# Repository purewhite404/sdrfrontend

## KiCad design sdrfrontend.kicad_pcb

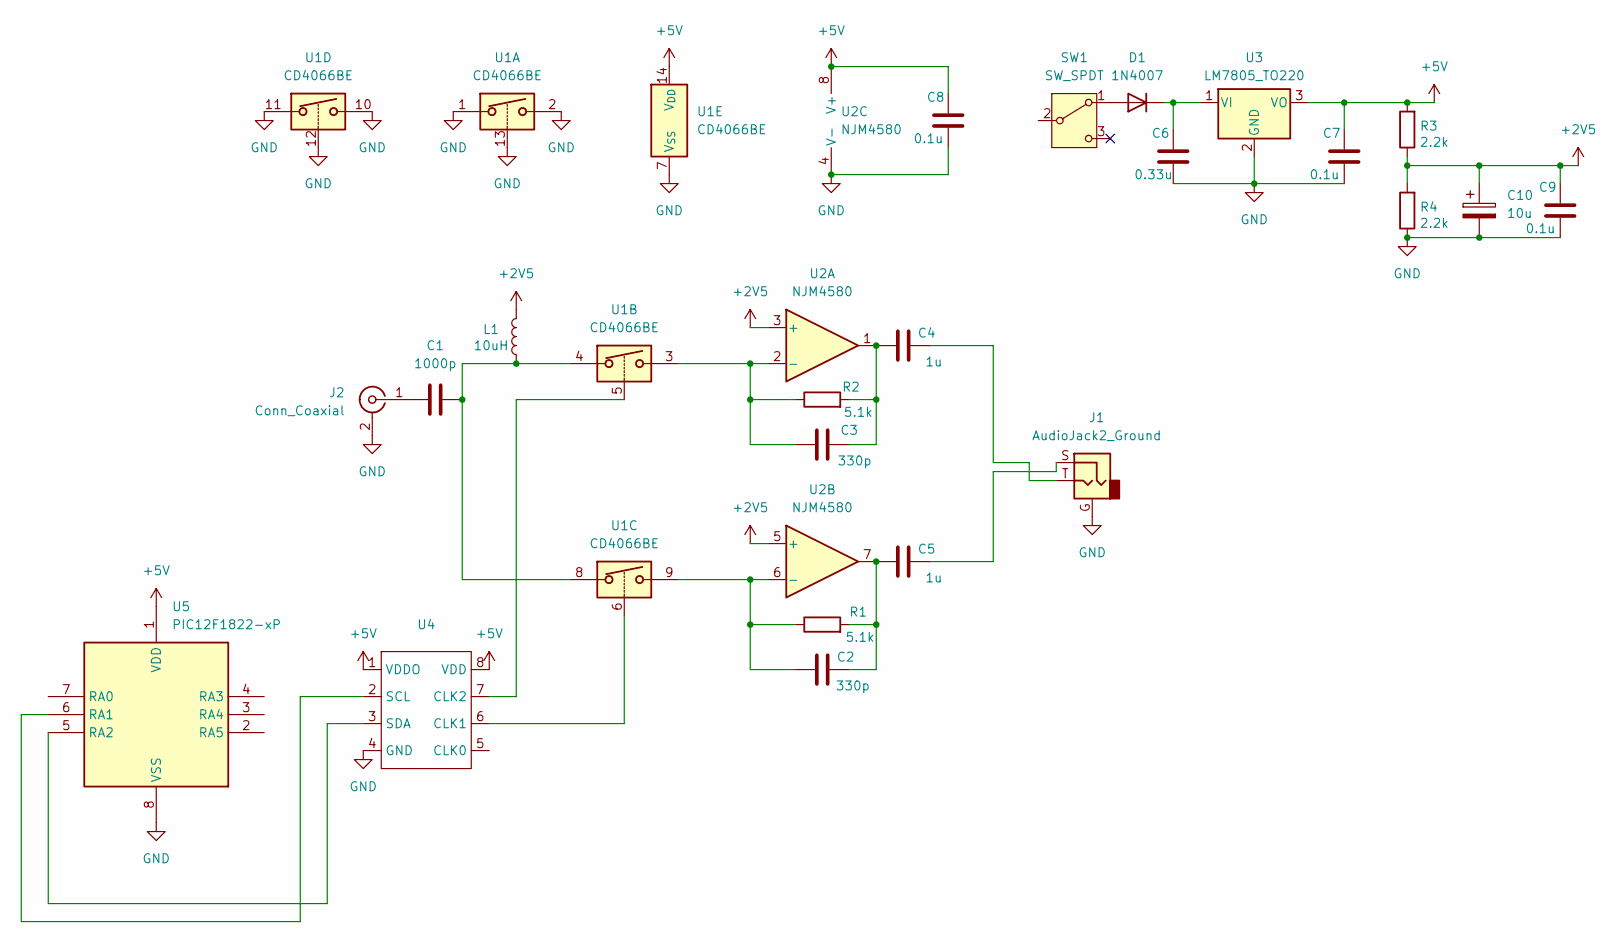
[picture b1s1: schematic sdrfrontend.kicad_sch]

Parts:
C1: 1000p; C_Disc_D3.0mm_W1.6mm_P2.50mm
C2, C3: 330p; C_Disc_D3.0mm_W1.6mm_P2.50mm
C4, C5: 1u; C_Disc_D3.0mm_W1.6mm_P2.50mm
C6: 0.33u; C_Disc_D3.0mm_W1.6mm_P2.50mm
C7, C8, C9: 0.1u; C_Disc_D3.0mm_W1.6mm_P2.50mm
C10: 10u; CP_Radial_D5.0mm_P2.50mm
D1: 1N4007; D_A-405_P7.62mm_Horizontal
J1: AudioJack2_Ground; 2.5jack
J2: Conn_Coaxial; SMA_Amphenol_132289_EdgeMount
L1: 10uH; L_Axial_L7.0mm_D3.3mm_P10.16mm_Horizontal_Fastron_MICC
R1, R2: 5.1k; R_Axial_DIN0207_L6.3mm_D2.5mm_P2.54mm_Vertical
R3, R4: 2.2k; R_Axial_DIN0207_L6.3mm_D2.5mm_P7.62mm_Horizontal
SW1: SW_SPDT; SW_Slide-03_Wuerth-WS-SLTV_10x2.5x6.4_P2.54mm
U1: CD4066BE; DIP-14_W7.62mm
U2: NJM4580; DIP-8_W7.62mm
U3: LM7805_TO220; TO-220-3_Vertical
U4: DIP-8_W7.62mm
U5: PIC12F1822-xP; DIP-8_W7.62mm

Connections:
+2V5: C9.1, C10.1, L1.2, R3.1, R4.2, U2.3 (+), U2.5 (+)
+5V: C7.1, C8.1, R3.2, U1.14 (V_{DD}), U2.8 (V+), U3.3 (VO), U4.1 (VDDO), U4.8 (VDD), U5.1 (VDD)
GND: C6.2, C7.2, C8.2, C9.2, C10.2, J1.G, J2.2 (Ext), R4.1, U1.1, U1.2, U1.7 (V_{SS}), U1.10, U1.11, U1.12, U1.13, U2.4 (V-), U3.2 (GND), U4.4 (GND), U5.8 (VSS)
unnamed: C1.2, L1.1, U1.4, U1.8
unnamed: C2.1, C5.2, R1.2, U2.7
unnamed: C3.1, C4.2, R2.2, U2.1
unnamed: C4.1, J1.T
unnamed: C5.1, J1.S
unnamed: D1.2 (A), SW1.1 (A)
unnamed: C6.1, D1.1 (K), U3.1 (VI)
unnamed: C1.1, J2.1 (In)
unnamed: C3.2, R2.1, U1.3, U2.2 (-)
unnamed: C2.2, R1.1, U1.9, U2.6 (-)
unnamed: U1.6, U4.6 (CLK1)
unnamed: U1.5, U4.7 (CLK2)
unnamed: U4.2 (SCL), U5.6 (RA1)
unnamed: U4.3 (SDA), U5.5 (RA2)

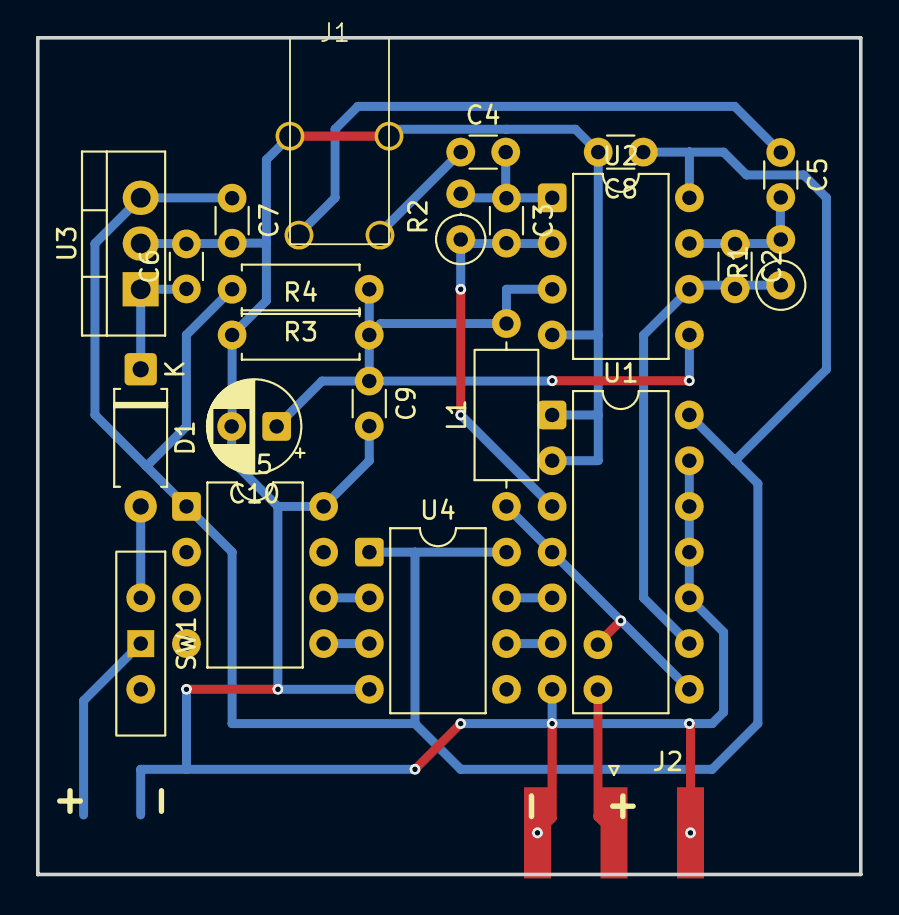
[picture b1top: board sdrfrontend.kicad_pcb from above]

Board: 2 copper layers, 45.7 x 46.5 mm, 24 parts (1 on the bottom side), 17 nets.

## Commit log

2025-05-09 init commit
2025-05-09 wiring parts
2025-05-10 make pcb
2025-05-10 add switch and sma conn
